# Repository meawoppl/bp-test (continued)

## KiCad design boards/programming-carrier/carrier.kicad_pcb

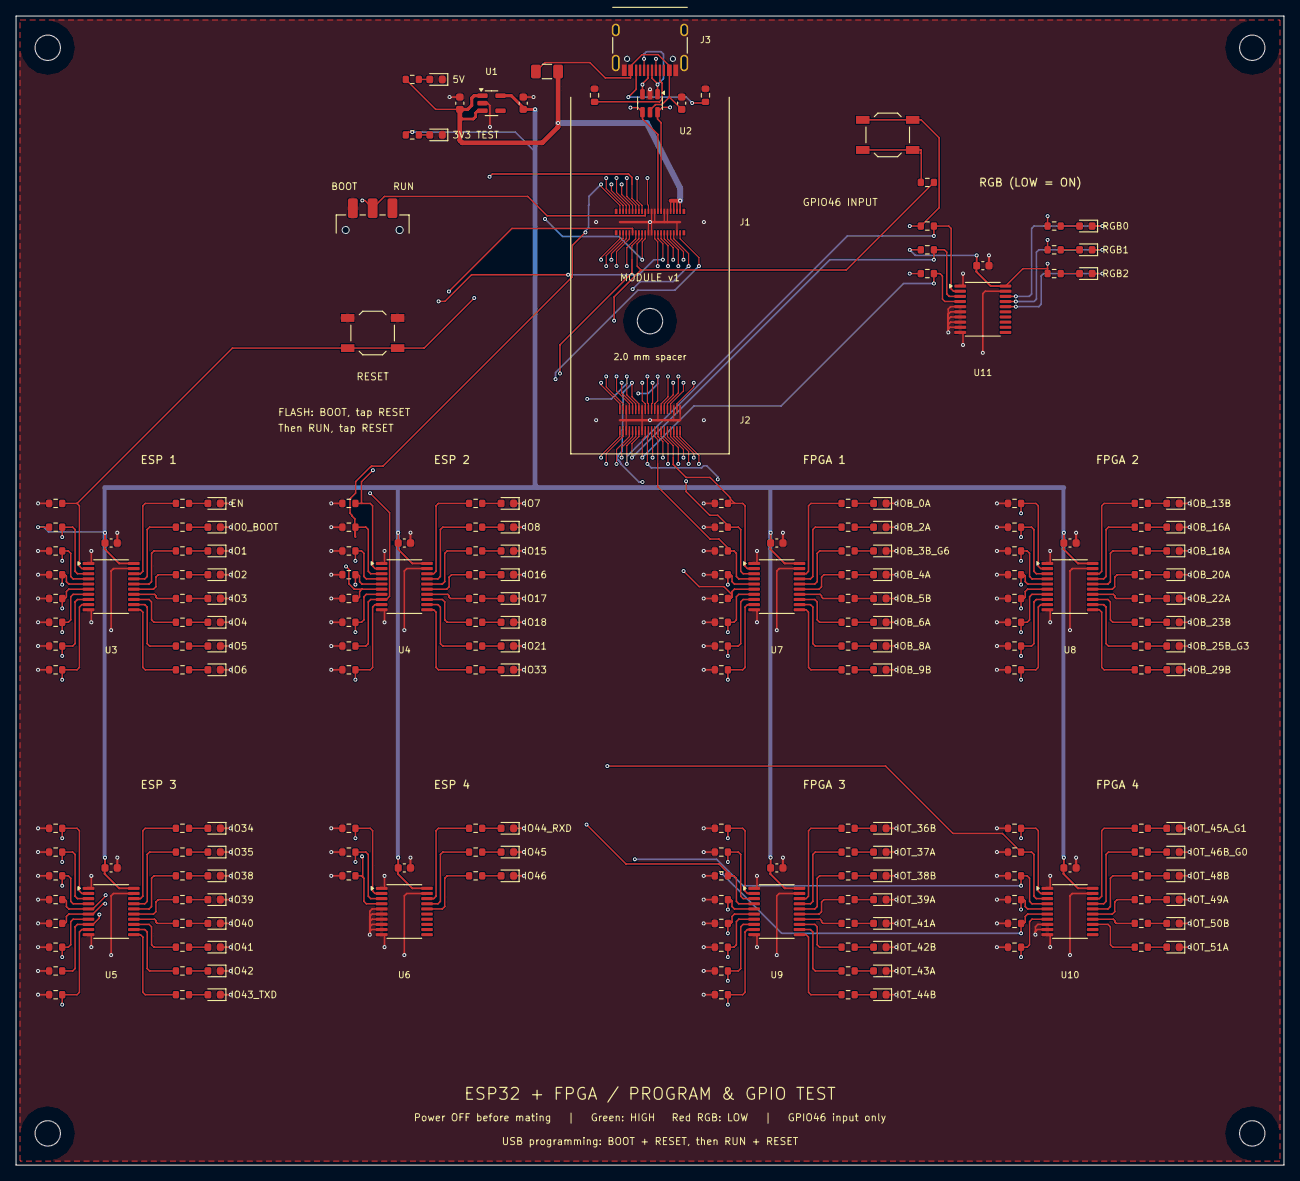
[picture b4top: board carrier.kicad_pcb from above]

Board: 4 copper layers, 160.0 x 145.0 mm, 222 parts (0 on the bottom side), 191 nets.

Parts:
C1, C2: 4.7uF; C_0603_1608Metric
C3, C10, C11, C12, C13, C14, C15, C16, C17, C18: 100nF; C_0603_1608Metric
D1, D2, D10, D11, D12, D13, D14, D15, D16, D17, D18, D19, D20, D21, D22, D23, D24, D25, D26, D27, D28, D29, D30, D31, D32, D33, D34, D35, D36, D42, D43, D44, D45, D46, D47, D48, D49, D50, D51, D52, D53, D54, D55, D56, D57, D58, D59, D60, D61, D62, D63, D64, D65, D66, D67, D68, D69, D70, D71: GREEN; LED_0603_1608Metric
D74, D75, D76: RED; LED_0603_1608Metric
F1: 500mA PTC; Fuse_1206_3216Metric
H1, H2, H3, H4, H5: M3; MountingHole_3.2mm_M3
J1: DF40C-40DP-0.4V(51); J1_Module_v1_Mate
J2: DF40C(2.0)-40DS-0.4V(51); J2_Module_v1_Mate
J3: USB-C USB2; USB_C_Receptacle_HRO_TYPE-C-31-M-12
R1, R2: 5.1kR; R_0603_1608Metric
R3: 2.2kR; R_0603_1608Metric
R4, R5, R10, R11, R12, R13, R14, R15, R16, R17, R18, R19, R20, R21, R22, R23, R24, R25, R26, R27, R28, R29, R30, R31, R32, R33, R34, R35, R36, R42, R43, R44, R45, R46, R47, R48, R49, R50, R51, R52, R53, R54, R55, R56, R57, R58, R59, R60, R61, R62, R63, R64, R65, R66, R67, R68, R69, R70, R71, R74, R75, R76: 1kR; R_0603_1608Metric
R110, R111, R112, R113, R114, R115, R116, R117, R118, R119, R120, R121, R122, R123, R124, R125, R126, R127, R128, R129, R130, R131, R132, R133, R134, R135, R136, R142, R143, R144, R145, R146, R147, R148, R149, R150, R151, R152, R153, R154, R155, R156, R157, R158, R159, R160, R161, R162, R163, R164, R165, R166, R167, R168, R169, R170, R171, R174, R175, R176: 100kR; R_0603_1608Metric
SW1: BOOT / RUN; SW_SPDT_CK_JS102011SAQN
SW2: RESET; SW_SPST_TL3342
SW3: GPIO46 INPUT; SW_SPST_TL3342
U1: AP2112K-3.3; SOT-23-5
U2: USBLC6-2SC6; SOT-23-6
U3, U4, U5, U6, U7, U8, U9, U10, U11: SN74LVC541APWR; TSSOP-20_4.4x6.5mm_P0.65mm

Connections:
+3V3_TEST: C2.1, C10.1, C11.1, C12.1, C13.1, C14.1, C15.1, C16.1, C17.1, C18.1, R4.1, R74.1, R75.1, R76.1, R111.2, R174.2, R175.2, R176.2, SW3.1, U1.5, U3.20, U4.20, U5.20, U6.20, U7.20, U8.20, U9.20, U10.20, U11.20
BUF_ESP_EN: R10.1, U3.18
BUF_ESP_GPIO0_BOOT: R11.1, U3.17
BUF_ESP_GPIO1: R12.1, U3.16
BUF_ESP_GPIO2: R13.1, U3.15
BUF_ESP_GPIO3: R14.1, U3.14
BUF_ESP_GPIO4: R15.1, U3.13
BUF_ESP_GPIO5: R16.1, U3.12
BUF_ESP_GPIO6: R17.1, U3.11
BUF_ESP_GPIO7: R18.1, U4.18
BUF_ESP_GPIO8: R19.1, U4.17
BUF_ESP_GPIO15: R20.1, U4.16
BUF_ESP_GPIO16: R21.1, U4.15
BUF_ESP_GPIO17: R22.1, U4.14
BUF_ESP_GPIO18: R23.1, U4.13
BUF_ESP_GPIO21: R24.1, U4.12
BUF_ESP_GPIO33: R25.1, U4.11
BUF_ESP_GPIO34: R26.1, U5.18
BUF_ESP_GPIO35: R27.1, U5.17
BUF_ESP_GPIO38: R28.1, U5.16
BUF_ESP_GPIO39: R29.1, U5.15
BUF_ESP_GPIO40: R30.1, U5.14
BUF_ESP_GPIO41: R31.1, U5.13
BUF_ESP_GPIO42: R32.1, U5.12
BUF_ESP_GPIO43_TXD: R33.1, U5.11
BUF_ESP_GPIO44_RXD: R34.1, U6.18
BUF_ESP_GPIO45: R35.1, U6.17
BUF_ESP_GPIO46: R36.1, U6.16
BUF_FPGA_IOB_0A: R42.1, U7.18
BUF_FPGA_IOB_2A: R43.1, U7.17
BUF_FPGA_IOB_3B_G6: R44.1, U7.16
BUF_FPGA_IOB_4A: R45.1, U7.15
BUF_FPGA_IOB_5B: R46.1, U7.14
BUF_FPGA_IOB_6A: R47.1, U7.13
BUF_FPGA_IOB_8A: R48.1, U7.12
BUF_FPGA_IOB_9B: R49.1, U7.11
BUF_FPGA_IOB_13B: R50.1, U8.18
BUF_FPGA_IOB_16A: R51.1, U8.17
BUF_FPGA_IOB_18A: R52.1, U8.16
BUF_FPGA_IOB_20A: R53.1, U8.15
BUF_FPGA_IOB_22A: R54.1, U8.14
BUF_FPGA_IOB_23B: R55.1, U8.13
BUF_FPGA_IOB_25B_G3: R56.1, U8.12
BUF_FPGA_IOB_29B: R57.1, U8.11
BUF_FPGA_IOT_36B: R58.1, U9.18
BUF_FPGA_IOT_37A: R59.1, U9.17
BUF_FPGA_IOT_38B: R60.1, U9.16
BUF_FPGA_IOT_39A: R61.1, U9.15
BUF_FPGA_IOT_41A: R62.1, U9.14
BUF_FPGA_IOT_42B: R63.1, U9.13
BUF_FPGA_IOT_43A: R64.1, U9.12
BUF_FPGA_IOT_44B: R65.1, U9.11
BUF_FPGA_IOT_45A_G1: R66.1, U10.18
BUF_FPGA_IOT_46B_G0: R67.1, U10.17
BUF_FPGA_IOT_48B: R68.1, U10.16
BUF_FPGA_IOT_49A: R69.1, U10.15
BUF_FPGA_IOT_50B: R70.1, U10.14
BUF_FPGA_IOT_51A: R71.1, U10.13
BUF_FPGA_RGB0: D74.1, U11.18
BUF_FPGA_RGB1: D75.1, U11.17
BUF_FPGA_RGB2: D76.1, U11.16
CC1: J3.A5, R1.1
CC2: J3.B5, R2.1
ESP_EN: J1.11, R110.1, SW2.2, U3.2
ESP_GPIO0_BOOT: J1.12, R111.1, SW1.2, U3.3
ESP_GPIO1: J1.13, R112.1, U3.4
ESP_GPIO2: J1.14, R113.1, U3.5
ESP_GPIO3: J1.15, R114.1, U3.6
ESP_GPIO4: J1.16, R115.1, U3.7
ESP_GPIO5: J1.17, R116.1, U3.8
ESP_GPIO6: J1.18, R117.1, U3.9
ESP_GPIO7: J1.19, R118.1, U4.2
ESP_GPIO8: J1.20, R119.1, U4.3
ESP_GPIO15: J1.35, R120.1, U4.4
ESP_GPIO16: J1.37, R121.1, U4.5
ESP_GPIO17: J1.36, R122.1, U4.6
ESP_GPIO18: J1.38, R123.1, U4.7
ESP_GPIO21: J1.40, R124.1, U4.8
ESP_GPIO33: J1.29, R125.1, U4.9
ESP_GPIO34: J1.32, R126.1, U5.2
ESP_GPIO35: J1.28, R127.1, U5.3
ESP_GPIO38: J1.39, R128.1, U5.4
ESP_GPIO39: J1.23, R129.1, U5.5
ESP_GPIO40: J1.21, R130.1, U5.6
ESP_GPIO41: J1.24, R131.1, U5.7
ESP_GPIO42: J1.25, R132.1, U5.8
ESP_GPIO43_TXD: J1.26, R133.1, U5.9
ESP_GPIO44_RXD: J1.27, R134.1, U6.2
ESP_GPIO45: J1.34, R135.1, U6.3
ESP_GPIO46: J1.33, R5.2, R136.1, U6.4
FPGA_IOB_0A: J2.35, R142.1, U7.2
FPGA_IOB_2A: J2.36, R143.1, U7.3
FPGA_IOB_3B_G6: J2.32, R144.1, U7.4
FPGA_IOB_4A: J2.37, R145.1, U7.5
FPGA_IOB_5B: J2.34, R146.1, U7.6
FPGA_IOB_6A: J2.40, R147.1, U7.7
FPGA_IOB_8A: J2.39, R148.1, U7.8
FPGA_IOB_9B: J2.38, R149.1, U7.9
FPGA_IOB_13B: J2.6, R150.1, U8.2
FPGA_IOB_16A: J2.4, R151.1, U8.3
FPGA_IOB_18A: J2.2, R152.1, U8.4
FPGA_IOB_20A: J2.7, R153.1, U8.5
FPGA_IOB_22A: J2.5, R154.1, U8.6
FPGA_IOB_23B: J2.10, R155.1, U8.7
FPGA_IOB_25B_G3: J2.12, R156.1, U8.8
FPGA_IOB_29B: J2.11, R157.1, U8.9
FPGA_IOT_36B: J2.14, R158.1, U9.2
FPGA_IOT_37A: J2.9, R159.1, U9.3
FPGA_IOT_38B: J2.15, R160.1, U9.4
FPGA_IOT_39A: J2.16, R161.1, U9.5
FPGA_IOT_41A: J2.17, R162.1, U9.6
FPGA_IOT_42B: J2.19, R163.1, U9.7
FPGA_IOT_43A: J2.20, R164.1, U9.8
FPGA_IOT_44B: J2.33, R165.1, U9.9
FPGA_IOT_45A_G1: J2.24, R166.1, U10.2
FPGA_IOT_46B_G0: J2.22, R167.1, U10.3
FPGA_IOT_48B: J2.21, R168.1, U10.4
FPGA_IOT_49A: J2.31, R169.1, U10.5
FPGA_IOT_50B: J2.25, R170.1, U10.6
FPGA_IOT_51A: J2.30, R171.1, U10.7
FPGA_RGB0: J2.26, R174.1, U11.2
FPGA_RGB1: J2.27, R175.1, U11.3
FPGA_RGB2: J2.29, R176.1, U11.4
GND: C1.2, C2.2, C3.2, C10.2, C11.2, C12.2, C13.2, C14.2, C15.2, C16.2, C17.2, C18.2, D1.1, D2.1, D10.1, D11.1, D12.1, D13.1, D14.1, D15.1, D16.1, D17.1, D18.1, D19.1, D20.1, D21.1, D22.1, D23.1, D24.1, D25.1, D26.1, D27.1, D28.1, D29.1, D30.1, D31.1, D32.1, D33.1, D34.1, D35.1, D36.1, D42.1, D43.1, D44.1, D45.1, D46.1, D47.1, D48.1, D49.1, D50.1, D51.1, D52.1, D53.1, D54.1, D55.1, D56.1, D57.1, D58.1, D59.1, D60.1, D61.1, D62.1, D63.1, D64.1, D65.1, D66.1, D67.1, D68.1, D69.1, D70.1, D71.1, J1.5, J1.6, J1.9, J1.10, J1.22, J1.30, J1.31, J2.1, J2.3, J2.8, J2.13, J2.18, J2.23, J2.28, J3.A1, J3.A12, J3.B1, J3.B12, J3.S1, R1.2, R2.2, R110.2, R112.2, R113.2, R114.2, R115.2, R116.2, R117.2, R118.2, R119.2, R120.2, R121.2, R122.2, R123.2, R124.2, R125.2, R126.2, R127.2, R128.2, R129.2, R130.2, R131.2, R132.2, R133.2, R134.2, R135.2, R136.2, R142.2, R143.2, R144.2, R145.2, R146.2, R147.2, R148.2, R149.2, R150.2, R151.2, R152.2, R153.2, R154.2, R155.2, R156.2, R157.2, R158.2, R159.2, R160.2, R161.2, R162.2, R163.2, R164.2, R165.2, R166.2, R167.2, R168.2, R169.2, R170.2, R171.2, SW1.1, SW2.1, U1.2, U2.2, U3.1, U3.10, U3.19, U4.1, U4.10, U4.19, U5.1, U5.10, U5.19, U6.1, U6.5, U6.6, U6.7, U6.8, U6.9, U6.10, U6.19, U7.1, U7.10, U7.19, U8.1, U8.10, U8.19, U9.1, U9.10, U9.19, U10.1, U10.8, U10.9, U10.10, U10.19, U11.1, U11.5, U11.6, U11.7, U11.8, U11.9, U11.10, U11.19
GPIO46_TEST: R5.1, SW3.2
LED_ESP_EN: D10.2, R10.2
LED_ESP_GPIO0_BOOT: D11.2, R11.2
LED_ESP_GPIO1: D12.2, R12.2
LED_ESP_GPIO2: D13.2, R13.2
LED_ESP_GPIO3: D14.2, R14.2
LED_ESP_GPIO4: D15.2, R15.2
LED_ESP_GPIO5: D16.2, R16.2
LED_ESP_GPIO6: D17.2, R17.2
LED_ESP_GPIO7: D18.2, R18.2
LED_ESP_GPIO8: D19.2, R19.2
LED_ESP_GPIO15: D20.2, R20.2
LED_ESP_GPIO16: D21.2, R21.2
LED_ESP_GPIO17: D22.2, R22.2
LED_ESP_GPIO18: D23.2, R23.2
LED_ESP_GPIO21: D24.2, R24.2
LED_ESP_GPIO33: D25.2, R25.2
LED_ESP_GPIO34: D26.2, R26.2
LED_ESP_GPIO35: D27.2, R27.2
LED_ESP_GPIO38: D28.2, R28.2
LED_ESP_GPIO39: D29.2, R29.2
LED_ESP_GPIO40: D30.2, R30.2
LED_ESP_GPIO41: D31.2, R31.2
LED_ESP_GPIO42: D32.2, R32.2
LED_ESP_GPIO43_TXD: D33.2, R33.2
LED_ESP_GPIO44_RXD: D34.2, R34.2
LED_ESP_GPIO45: D35.2, R35.2
LED_ESP_GPIO46: D36.2, R36.2
LED_FPGA_IOB_0A: D42.2, R42.2
LED_FPGA_IOB_2A: D43.2, R43.2
LED_FPGA_IOB_3B_G6: D44.2, R44.2
LED_FPGA_IOB_4A: D45.2, R45.2
LED_FPGA_IOB_5B: D46.2, R46.2
LED_FPGA_IOB_6A: D47.2, R47.2
LED_FPGA_IOB_8A: D48.2, R48.2
LED_FPGA_IOB_9B: D49.2, R49.2
LED_FPGA_IOB_13B: D50.2, R50.2
LED_FPGA_IOB_16A: D51.2, R51.2
LED_FPGA_IOB_18A: D52.2, R52.2
LED_FPGA_IOB_20A: D53.2, R53.2
LED_FPGA_IOB_22A: D54.2, R54.2
LED_FPGA_IOB_23B: D55.2, R55.2
LED_FPGA_IOB_25B_G3: D56.2, R56.2
LED_FPGA_IOB_29B: D57.2, R57.2
LED_FPGA_IOT_36B: D58.2, R58.2
LED_FPGA_IOT_37A: D59.2, R59.2
LED_FPGA_IOT_38B: D60.2, R60.2
LED_FPGA_IOT_39A: D61.2, R61.2
LED_FPGA_IOT_41A: D62.2, R62.2
LED_FPGA_IOT_42B: D63.2, R63.2
LED_FPGA_IOT_43A: D64.2, R64.2
LED_FPGA_IOT_44B: D65.2, R65.2
LED_FPGA_IOT_45A_G1: D66.2, R66.2
LED_FPGA_IOT_46B_G0: D67.2, R67.2
LED_FPGA_IOT_48B: D68.2, R68.2
LED_FPGA_IOT_49A: D69.2, R69.2
LED_FPGA_IOT_50B: D70.2, R70.2
LED_FPGA_IOT_51A: D71.2, R71.2
LED_FPGA_RGB0: D74.2, R74.2
LED_FPGA_RGB1: D75.2, R75.2
LED_FPGA_RGB2: D76.2, R76.2
P3_LED: D2.2, R4.2
P5_LED: D1.2, R3.2
USB_D+: J1.7, J3.A6, J3.B6, U2.1, U2.6
USB_D-: J1.8, J3.A7, J3.B7, U2.3, U2.4
VBUS: C3.1, F1.1, J3.A4, J3.A9, J3.B4, J3.B9, U2.5
VIN_5V: C1.1, F1.2, J1.1, J1.2, J1.3, J1.4, R3.1, U1.1, U1.3

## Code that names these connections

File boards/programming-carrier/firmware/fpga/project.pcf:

# GENERATED by tools/gen_pinmap.py from docs/led-map.json and the module v1 netlist.
# Do not edit by hand.

# Module-internal ESP32-S2 link (FPGA SPI configuration pins, reused at runtime)
set_io SPI_SO     14
set_io SPI_SCK    15
set_io SPI_SS_N   16
set_io SPI_SI     17

# Carrier monitor outputs: fpga_out[n] -> LED, bit order = led-map.json order
set_io fpga_out[0]  46  # D42 U7 FPGA_IOB_0A J2-35
set_io fpga_out[1]  47  # D43 U7 FPGA_IOB_2A J2-36
set_io fpga_out[2]  44  # D44 U7 FPGA_IOB_3B_G6 J2-32
set_io fpga_out[3]  48  # D45 U7 FPGA_IOB_4A J2-37
set_io fpga_out[4]  45  # D46 U7 FPGA_IOB_5B J2-34
set_io fpga_out[5]   2  # D47 U7 FPGA_IOB_6A J2-40
set_io fpga_out[6]   4  # D48 U7 FPGA_IOB_8A J2-39
set_io fpga_out[7]   3  # D49 U7 FPGA_IOB_9B J2-38
set_io fpga_out[8]   6  # D50 U8 FPGA_IOB_13B J2-6
set_io fpga_out[9]   9  # D51 U8 FPGA_IOB_16A J2-4
set_io fpga_out[10] 10  # D52 U8 FPGA_IOB_18A J2-2
set_io fpga_out[11] 11  # D53 U8 FPGA_IOB_20A J2-7
set_io fpga_out[12] 12  # D54 U8 FPGA_IOB_22A J2-5
set_io fpga_out[13] 21  # D55 U8 FPGA_IOB_23B J2-10
set_io fpga_out[14] 20  # D56 U8 FPGA_IOB_25B_G3 J2-12
set_io fpga_out[15] 19  # D57 U8 FPGA_IOB_29B J2-11
set_io fpga_out[16] 25  # D58 U9 FPGA_IOT_36B J2-14
set_io fpga_out[17] 23  # D59 U9 FPGA_IOT_37A J2-9
set_io fpga_out[18] 27  # D60 U9 FPGA_IOT_38B J2-15
set_io fpga_out[19] 26  # D61 U9 FPGA_IOT_39A J2-16
set_io fpga_out[20] 28  # D62 U9 FPGA_IOT_41A J2-17
set_io fpga_out[21] 31  # D63 U9 FPGA_IOT_42B J2-19
set_io fpga_out[22] 32  # D64 U9 FPGA_IOT_43A J2-20
set_io fpga_out[23] 34  # D65 U9 FPGA_IOT_44B J2-33
set_io fpga_out[24] 37  # D66 U10 FPGA_IOT_45A_G1 J2-24
set_io fpga_out[25] 35  # D67 U10 FPGA_IOT_46B_G0 J2-22
set_io fpga_out[26] 36  # D68 U10 FPGA_IOT_48B J2-21
set_io fpga_out[27] 43  # D69 U10 FPGA_IOT_49A J2-31
set_io fpga_out[28] 38  # D70 U10 FPGA_IOT_50B J2-25
set_io fpga_out[29] 42  # D71 U10 FPGA_IOT_51A J2-30

# RGB current sinks (SB_RGBA_DRV), shared with module D1 and carrier red monitors
set_io RGB0       39  # D74 FPGA_RGB0 J2-26
set_io RGB1       40  # D75 FPGA_RGB1 J2-27
set_io RGB2       41  # D76 FPGA_RGB2 J2-29

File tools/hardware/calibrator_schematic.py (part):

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def custom_map(ref):
 c=parts[ref]
 if ref in ['J1','J2']:
  ground=[n for n,v in c['pins'].items() if v=='GND'];supply=[n for n,v in c['pins'].items() if v in ['VIN_5V','USB_VBUS']];other=sorted([n for n in c['pins'] if n not in ground+supply],key=int);half=(len(other)+1)//2
  m={n:((-17.78 if i<half else 17.78),38.1-(i%half)*5.08,(0 if i<half else 180)) for i,n in enumerate(other)}
  m.update({n:((i-(len(ground)-1)/2)*2.54,-48.26,90) for i,n in enumerate(ground)})
  m.update({n:((i-(len(supply)-1)/2)*5.08,48.26,270) for i,n in enumerate(supply)})
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for ref,x in [('J1',73.66),('J2',205.74)]:
 place(ref,x,82.55)
 gs=[n for n,vv in parts[ref]['pins'].items() if vv=='GND'];bus(ref,gs,134.62,'GND')
 vs=[n for n,vv in parts[ref]['pins'].items() if vv in ['VIN_5V','USB_VBUS']]
 if vs:bus(ref,vs,29.21,parts[ref]['pins'][vs[0]])
 for n in parts[ref]['pins']:
  if (ref,n) not in covered:port(ref,n,7.62)
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path(P('U11',1),(438.15,33.02),(408.94,33.02));power('USB_VBUS',438.15,33.02)
place('R164',478.79,93.98,270)
path(P('U11',9),(478.79,78.74),P('R164',1));power('GND',*P('R164',2))
label('PD_ISET',466.09,78.74)
for ref,x,n,y in [('R167',478.79,'6',63.5),('R168',502.92,'7',68.58)]:
 place(ref,x,45.72,270);path(P(ref,2),(snap(x),snap(y)),P('U11',n));junction((x,y));power('+3V3_LOGIC',*P(ref,1));label(parts[ref]['pins']['2'],x,y)
note('5 V ONLY: VSET grounded / ISET 22.6k = 3 A / I2C 0x08',353.06,121.92,1.2)
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path(P('U14',3),(666.75,53.34),(666.75,44.45),(641.35,44.45));path(P('U14',4),(666.75,58.42),(666.75,53.34));junction((666.75,53.34));power('USB_VBUS',641.35,44.45)
port('U14',2,20.32)
place('R169',657.86,107.95,270);path(P('R169',1),(657.86,68.58),P('U14',2));junction((657.86,68.58));power('GND',*P('R169',2))
place('C68',673.1,102.87,270);path(P('U14',1),(692.15,87.63),(673.1,87.63),P('C68',1));label('USB_DVDT',673.1,87.63);power('GND',*P('C68',2))
place('R170',737.87,102.87,270);path(P('U14',7),(709.93,87.63),(737.87,87.63),P('R170',1));label('USB_ILIM',715.01,87.63);power('GND',*P('R170',2));bus('U14',['8','9'],81.28,'GND')
path(P('U14',5),(746.76,53.34));power('VIN_5V',746.76,53.34)
place('R176',787.4,100.33);path((737.87,87.63),(760.73,87.63),(760.73,100.33),P('R176',1));junction((737.87,87.63))
bypass('C78',805.18,121.92,'ESP_GPIO3',upper=100.33);path(P('R176',2),(805.18,100.33));label('ESP_GPIO3',805.18,100.33)
# One real power indicator, wired as LED plus its own resistor.
place('R3',774.7,58.42,270);place('D1',774.7,83.82,270)
path(P('R3',1),(774.7,45.72));power('VIN_5V',774.7,45.72)
path(P('R3',2),P('D1',2));label(parts['R3']['pins']['2'],774.7,71.12);power('GND',*P('D1',1))
note('ESP_GPIO4 enables loads; 820R sets ~2.48 A. ADC: 0.226 V/A nominal, switched loads only.',486.41,140.97,1.1)
note('Module and logic boot from raw 5 V. GPIO7/8 read PD status over I2C; firmware budgets current before enabling loads.',486.41,146.05,1.1)
# ---- GNSS receiver and active-antenna bias ------------------------------------
box('GNSS / PPS reference and active antenna bias',12.7,156.21,236.22,118.11)
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port('U6',2,10.16);port('U6',3,10.16);port('U6',5,10.16)
# One visible PPS tree: two upward, independently damped timing destinations,
# and the indicator resistor/LED directly below the common node.
path(P('U6',4),(30.48,218.44));label('GPS_PPS',91.44,218.44)
for ref,x,title in [('R6',30.48,'FPGA PPS / G0'),('R7',73.66,'ESP32 PPS / GPIO38')]:
 place(ref,x,195.58,90);path(P(ref,1),(x,218.44))
 path(P(ref,2),(x,187.96));label(parts[ref]['pins']['2'],x,187.96)
 note(title,x,176.53,1.1)
place('R179',30.48,233.68,270);place('D74',30.48,254,270)
path((30.48,218.44),P('R179',1));path(P('R179',2),P('D74',2));label('PPS_LED_A',30.48,245.11)
power('GND',*P('D74',1))
note('PPS indicator',43.18,254,1.1)
# Compact VCC_RF-powered bias tee adjacent to RF_IN.
place('R5',194.31,198.12);path(P('U6',14),P('R5',1));label('ANT_PWR',166.37,198.12)
place('L1',222.25,205.74,90);path(P('R5',2),(222.25,198.12),P('L1',2));label('ANT_BIAS',209.55,198.12)
bypass('C10',207.01,204.47,'ANT_BIAS',upper=198.12)
place('J5',238.76,218.44);path(P('U6',11),P('J5',1));label('GNSS_RF',170.18,218.44)
path(P('L1',1),(222.25,218.44));port('J5',2)
# Reset input stays below the UART/trigger labels, clear of the PPS tree.
place('R180',93.98,238.76);path(P('U6',9),P('R180',2));label('GPS_RESET_N',104.14,238.76)
port('R180',1,3.81)
def translate_section(first, previous_refs, dx, dy):
 # Move a presentation block, including its fields, power symbols and unused-pin stubs.
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box('Trigger input / 5 V TTL / threshold ~2.5 V',322.58,156.21,236.22,118.11)
place('J6',340.36,193.04);place('R8',374.65,193.04);place('U9',419.1,198.12)
# Input SMA points left graphically; lead exits and loops below the connector to R8.
path(P('J6',1),(327.66,193.04),(327.66,182.88),(359.41,182.88),(359.41,193.04),P('R8',1));label('TRIGGER_IN',346.71,182.88);port('J6',2)
path(P('R8',2),P('U9',3));label('TRIGGER_LIMIT',382.27,193.04)
bypass('C75',381,208.28,'TRIGGER_LIMIT',upper=193.04);junction((381,193.04))
place('R9',391.16,208.28,270);path(P('R9',1),(391.16,193.04));junction((391.16,193.04));power('GND',*P('R9',2))
# 2.5 V threshold divider and filter directly feed IN-.
place('R160',368.3,216.535,270);place('R161',368.3,245.11,270)
power('VIN_5V',*P('R160',1));path(P('R160',2),(368.3,231.14),P('R161',1));power('GND',*P('R161',2))
path((368.3,231.14),(401.32,231.14),(401.32,203.2),P('U9',1));label('TRIGGER_VREF',375.92,231.14)
bypass('C13',391.16,246.38,'TRIGGER_VREF',upper=231.14);junction((391.16,231.14))
bypass('C14',439.42,176.53,'VIN_5V',upper=168.91);path(P('U9',4),(419.1,168.91),(439.42,168.91));power('VIN_5V',419.1,168.91);bus('U9',['2','6'],218.44,'GND')
place('U7',480.06,193.04);path(P('U9',5),P('U7',2));label('TRIGGER_5V',441.96,193.04)
bypass('C11',501.65,175.26,'+3V3_GPS',upper=170.18);path(P('U7',5),(480.06,170.18),(501.65,170.18));power('+3V3_GPS',480.06,170.18);port('U7',3)
for ref,y in [('R80',193.04),('R81',208.28)]:
 place(ref,530.86,y);path(P('U7',4),(515.62,193.04),(515.62,snap(y)),P(ref,1));port(ref,2,3.81)
label('TRIGGER_3V3',500.38,193.04)
translate_section(section_start,section_refs,-66.04,0)
# ---- External trigger output --------------------------------------------------
box('Trigger output / 5 V TTL',500.38,156.21,139.7,118.11)
section_start=len(items);section_refs=set(placed)
# Grounded enable, input pulldown and series output damping.
place('U10',474.98,248.92);place('R162',509.27,248.92);place('J7',547.37,248.92)
path(P('U10',4),P('R162',1));label('TRIGGER_DRV',490.22,248.92);path(P('R162',2),P('J7',1));label('TRIGGER_OUT',519.43,248.92);port('J7',2)
place('R163',444.5,256.54,270);path(P('U10',2),(444.5,248.92),P('R163',1));label('FPGA_IOT_51A',429.26,248.92);path((429.26,248.92),(444.5,248.92));power('GND',*P('R163',2));bus('U10',['1','3'],267.97,'GND')
bypass('C15',501.65,231.14,'VIN_5V',upper=223.52);path(P('U10',5),(474.98,223.52),(492.76,223.52),(501.65,223.52));power('VIN_5V',492.76,223.52)
translate_section(section_start,section_refs,78.74,-40.64)
# ---- OCXO supply and clock ----------------------------------------------------
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for ref,x in [('C71',713.74),('C73',731.52),('C74',749.3)]:
 bypass(ref,x,203.2,'+3V3_OCXO',upper=189.23)
path(P('U15',5),(706.12,199.39),(706.12,189.23));bus('U15',['3','6'],227.33,'GND')
place('R178',665.48,219.71,270);path(P('R178',1),(665.48,199.39),P('U15',1));label('ESP_GPIO5',665.48,212.09,right=True);power('GND',*P('R178',2))
place('R173',805.18,222.25,270)
path(P('Y1',3),(805.18,204.47),P('R173',1));label('OCXO_CLK',800.1,204.47,right=True)
path(P('R173',2),(805.18,238.76));label(parts['R173']['pins']['2'],805.18,238.76,right=True,stub=False)
port('Y1',2)
note('SOT-223 heat spreader below OCXO; GPIO5 enables.',654.05,250.19,1.0)
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note('M3 spacer + four corner mounts.',617.22,373.38,1.0)
box('Date / UTC / GPS status OLED',706.12,281.94,119.38,97.79)
place('J8',777.24,337.82)
for ref,x,pin,net in [('R174',737.87,3,'ESP_GPIO2'),('R175',753.11,4,'ESP_GPIO1')]:
 place(ref,x,309.88,270);path(P(ref,1),(x,297.18));path(P(ref,2),(x,P('J8',pin)[1]),P('J8',pin));label(net,x-20.32,P('J8',pin)[1]);path((x-20.32,P('J8',pin)[1]),(x,P('J8',pin)[1]))
path((737.87,297.18),(753.11,297.18),(777.24,297.18));path((777.24,297.18),P('J8',2));power('+3V3_LOGIC',777.24,297.18)
for ref,x in [('C76',802.64),('C77',817.88)]:
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
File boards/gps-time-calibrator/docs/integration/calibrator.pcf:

# GPS calibrator RFC v1 reference pin constraints. Port names must match NEW HDL.
# PCF does not supply clock/CDC constraints or implement safe reset behavior.
set_io FSPI_CLK 15
set_io FSPI_MOSI 17
set_io FSPI_MISO 14
set_io FSPI_CS 16
set_io OCXO_10M 44
set_io GPS_PPS 35
set_io TRIGGER_IN 38
set_io TRIGGER_OUT 42
set_io LED_OE_N 34
set_io LED_BITS[15] 10 # J2.2, FPGA_IOB_18A
set_io LED_BITS[14] 9 # J2.4, FPGA_IOB_16A
set_io LED_BITS[13] 12 # J2.5, FPGA_IOB_22A
set_io LED_BITS[12] 6 # J2.6, FPGA_IOB_13B
set_io LED_BITS[11] 11 # J2.7, FPGA_IOB_20A
set_io LED_BITS[10] 23 # J2.9, FPGA_IOT_37A
set_io LED_BITS[9] 21 # J2.10, FPGA_IOB_23B
set_io LED_BITS[8] 19 # J2.11, FPGA_IOB_29B
set_io LED_BITS[7] 20 # J2.12, FPGA_IOB_25B_G3
set_io LED_BITS[6] 25 # J2.14, FPGA_IOT_36B
set_io LED_BITS[5] 27 # J2.15, FPGA_IOT_38B
set_io LED_BITS[4] 26 # J2.16, FPGA_IOT_39A
set_io LED_BITS[3] 28 # J2.17, FPGA_IOT_41A
set_io LED_BITS[2] 31 # J2.19, FPGA_IOT_42B
set_io LED_BITS[1] 32 # J2.20, FPGA_IOT_43A
set_io LED_BITS[0] 36 # J2.21, FPGA_IOT_48B
# Optional onboard RGB ports, only if instantiated in HDL:
# set_io RGB0 39
# set_io RGB1 40
# set_io RGB2 41

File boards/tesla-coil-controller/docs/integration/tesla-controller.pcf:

# Tesla carrier signal constraints for the UP5K-SG48 module.
# Port names must match the consuming FPGA top level.
# Generated from tesla_fpga_pinmap.py and icd-v1-pinout.csv.
# J2.2: FPGA_IOB_18A
set_io GDT2_L_HI 10
# J2.4: FPGA_IOB_16A
set_io GDT2_L_LO 9
# J2.5: FPGA_IOB_22A
set_io GDT2_R_HI 12
# J2.6: FPGA_IOB_13B
set_io GDT2_R_LO 6
# J2.7: FPGA_IOB_20A
set_io GDT1_L_HI 11
# J2.9: FPGA_IOT_37A
set_io GDT1_L_LO 23
# J2.10: FPGA_IOB_23B
set_io GDT1_R_HI 21
# J2.11: FPGA_IOB_29B
set_io GDT1_R_LO 19
# J2.22: FPGA_IOT_46B_G0
set_io CT1_ZERO 35
# J2.24: FPGA_IOT_45A_G1
set_io CT2_ZERO 37
# J2.31: FPGA_IOT_49A
set_io ADC_CONVST 43
# J2.32: FPGA_IOB_3B_G6
set_io ADC_RESET 44
# J2.33: FPGA_IOT_44B
set_io ADC_SCLK 34
# J2.34: FPGA_IOB_5B
set_io ADC_CS_N 45
# J2.35: FPGA_IOB_0A
set_io ADC_BUSY 46
# J2.36: FPGA_IOB_2A
set_io ADC_SDI 47
# J2.37: FPGA_IOB_4A
set_io ADC_DOUT_D 48
# J2.38: FPGA_IOB_9B
set_io ADC_DOUT_C 3
# J2.39: FPGA_IOB_8A
set_io ADC_DOUT_B 4
# J2.40: FPGA_IOB_6A
set_io ADC_DOUT_A 2

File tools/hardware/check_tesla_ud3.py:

#!/usr/bin/env python3
"""Independent channel contract checks and illustrative differential CT filter sweep.
Not a vendor choke macromodel: leakage is swept; no common-mode attenuation claim.
"""
import json,itertools
from pathlib import Path
import numpy as np
import matplotlib
matplotlib.use('Agg')
import matplotlib.pyplot as plt
D=Path(__file__).resolve().parents[2]/'boards/tesla-coil-controller'
p=json.loads((D/'docs/circuit.json').read_text())
from tesla_output import COMMANDS,CONTACTS
assert len(set(COMMANDS))==8
assert set(COMMANDS).issubset(p['J2']['pins'].values())
assert all(r not in p for r in ['U50','U55','C500','C501','R504'])
assert not any(n=='DRIVE_ARM' for part in p.values() for n in part['pins'].values())
for ch in range(2):
 for i in range(4):
  n=COMMANDS[ch*4+i]
  r='R'+str((505 if ch==0 else 513)+i)
  assert p[r]['pins']=={'1':n,'2':n+'_BUS'}
 for leg in range(2):
  d=p['U'+str(51+ch*2+leg)]['pins']
  assert [d['5'],d['6']]==[n+'_BUS' for n in COMMANDS[ch*4+leg*2:ch*4+leg*2+2]]
assert p['L40']['pins']=={'1':'CT1_CABLE_P','2':'CT1_RAW','4':'CT1_CABLE_N','3':'GND'}
assert p['J40']['pins']=={'1':'CT1_CABLE_P','2':'CT1_CABLE_N'}
for r in ['R400','R401','D40','C429']:assert p[r]['pins']=={'1':'CT1_RAW','2':'GND'}
assert p['C427']['pins']=={'1':'CT1_CABLE_P','2':'GND'}
assert p['C428']['pins']=={'1':'CT1_CABLE_N','2':'GND'}
def transfer(freq,leak):
 w=2*np.pi*freq;jw=1j*w;g=1/(.05+jw*leak/2)
 # Differential leakage equivalent, matched 150pF on cable conductors,
 # 1nF across 10R burden, ideal current source P->N. Both choke DCRs included.
 a=np.array([[g+jw*150e-12,0,-g],[0,g+jw*150e-12,0],[-g,0,g+.1+jw*1e-9]])
 return np.linalg.solve(a,np.array([1,-1,0]))[2]/10
f=np.geomspace(1e3,1e6,600);results=[]
plt.rcParams.update({'figure.facecolor':'#1a1b26','axes.facecolor':'#1a1b26','text.color':'#c0caf5','axes.labelcolor':'#c0caf5','xtick.color':'#c0caf5','ytick.color':'#c0caf5','axes.edgecolor':'#565f89'})
fig,axs=plt.subplots(2,1,figsize=(9,6),sharex=True)
for leak,col in zip([0,0.2e-6,2e-6],['#7aa2f7','#9ece6a','#e0af68']):
 h=np.array([transfer(x,leak) for x in f]);h30=transfer(30000,leak)
 results.append(dict(assumed_differential_leakage_uH=leak*1e6,gain_at_30k=float(abs(h30)),phase_deg_at_30k=float(np.angle(h30,deg=True)),delay_ns_at_30k=float(-np.angle(h30)/(2*np.pi*30000)*1e9)))
 axs[0].semilogx(f,20*np.log10(abs(h)),color=col,label=f'Assumed leakage {leak*1e6:g} µH')
 axs[1].semilogx(f,np.angle(h,deg=True),color=col)
for ax in axs:ax.axvline(30000,color='#bb9af7',ls='--');ax.grid(alpha=.18)
axs[0].set_ylabel('Gain relative to 10 Ω burden (dB)');axs[1].set_ylabel('Added phase (degrees)');axs[1].set_xlabel('Frequency (Hz)');axs[0].legend(facecolor='#1a1b26',labelcolor='#c0caf5')
fig.suptitle('CT input filter: differential small-signal model\nIdeal CT, linear parts; choke leakage assumed, not measured')
fig.tight_layout();out=D/'docs/cst';out.mkdir(exist_ok=True)
fig.savefig(out/'cable-filter-response.png',dpi=160)
(out/'cable-filter-results.json').write_text(json.dumps({'model':'Ideal current source, 50mΩ/winding, 150pF cable shunts, 1nF burden shunt; no TVS/cable/CT parasitics or core saturation','results':results},indent=2)+'\n')
print('Independent command paths and filter topology verified.');print(json.dumps(results,indent=2))

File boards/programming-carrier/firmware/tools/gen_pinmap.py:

#!/usr/bin/env python3
"""Generate the fixture PCF and ESP channel table from the carrier LED map.

Inputs:
  docs/led-map.json                                  carrier monitor channels
  ../esp32-fpga-module/fab/checks/module-netlist.xml module v1 connector/package pins

Outputs:
  firmware/fpga/project.pcf
  firmware/firmware/main/carrier_map.h

Run from anywhere: python3 boards/programming-carrier/firmware/tools/gen_pinmap.py
"""
import json
import re
import xml.etree.ElementTree as ET
from pathlib import Path

HERE = Path(__file__).resolve().parent
PROJECT = HERE.parent
CARRIER = PROJECT.parent
LED_MAP = CARRIER / "docs/led-map.json"
NETLIST = CARRIER.parent / "esp32-fpga-module/fab/checks/module-netlist.xml"

# FPGA pins used by the module-internal ESP32 link (LINK_* nets).
FPGA_SPI = {"SPI_SO": "LINK_MISO", "SPI_SCK": "LINK_SCK", "SPI_SS_N": "LINK_CS_N", "SPI_SI": "LINK_MOSI"}

# README "Pin classes": what the firmware may do with each ESP signal.
ESP_CLASS = {
    "ESP_EN": "CH_OBSERVE",          # chip enable; SW2 reset tests it
    "ESP_GPIO0_BOOT": "CH_OBSERVE",  # boot strap; SW1 controls it
    "ESP_GPIO45": "CH_OPT_IN",       # flash-voltage strap; separate opt-in test
    "ESP_GPIO46": "CH_INPUT",        # input only; SW3 button
}


def load_nets():
    root = ET.parse(NETLIST).getroot()
    nets = {}
    for net in root.iter("net"):
        name = net.get("name").lstrip("/")
        nets[name] = {n.get("ref"): n.get("pin") for n in net.iter("node")}
    return nets


def main():
    leds = json.loads(LED_MAP.read_text())
    nets = load_nets()

    channels = []
    fpga_bit = 0
    for e in leds:
        sig = e["signal"]
        nodes = nets[sig]
        conn = "J1" if "J1" in nodes else "J2"
        ch = {
            "signal": sig,
            "led": e["led"],
            "buffer": e["buffer"],
            "bank": e["bank"],
            "active_low": e["active_low"],
            "conn": conn,
            "conn_pin": int(nodes[conn]),
        }
        if e["bank"] == "ESP":
            ch["pkg_pin"] = int(nodes["U1"])
            m = re.match(r"ESP_GPIO(\d+)", sig)
            ch["gpio"] = int(m.group(1)) if m else -1
            ch["cls"] = ESP_CLASS.get(sig, "CH_OUTPUT")
            ch["index"] = ch["gpio"]
        elif e["bank"] == "FPGA":
            ch["pkg_pin"] = int(nodes["U2"])
            ch["cls"] = "CH_OUTPUT"
            ch["index"] = fpga_bit
            fpga_bit += 1
        else:
            ch["pkg_pin"] = int(nodes["U2"])
            ch["cls"] = "CH_RGB"
            ch["index"] = int(sig[-1])
        channels.append(ch)

    assert fpga_bit == 30, fpga_bit

    # ---- PCF ----
    pcf = [
        "# GENERATED by tools/gen_pinmap.py from docs/led-map.json and the module v1 netlist.",
        "# Do not edit by hand.",
        "",
        "# Module-internal ESP32-S2 link (FPGA SPI configuration pins, reused at runtime)",
    ]
    for port, net in FPGA_SPI.items():
        pcf.append(f"set_io {port:<10} {nets[net]['U2']}")
    pcf += ["", "# Carrier monitor outputs: fpga_out[n] -> LED, bit order = led-map.json order"]
    for ch in channels:
        if ch["bank"] == "FPGA":
            port = f"fpga_out[{ch['index']}]"
            pcf.append(f"set_io {port:<12} {ch['pkg_pin']:>2}  # {ch['led']} {ch['buffer']} {ch['signal']} {ch['conn']}-{ch['conn_pin']}")
    pcf += ["", "# RGB current sinks (SB_RGBA_DRV), shared with module D1 and carrier red monitors"]
    for ch in channels:
        if ch["bank"] == "RGB":
            pcf.append(f"set_io RGB{ch['index']:<7} {ch['pkg_pin']}  # {ch['led']} {ch['signal']} {ch['conn']}-{ch['conn_pin']}")
    (PROJECT / "fpga/project.pcf").write_text("\n".join(pcf) + "\n")

    # ---- C header ----
    banks = []
    for ch in channels:
        if ch["buffer"] not in banks:
            banks.append(ch["buffer"])
    h = [
        "// GENERATED by tools/gen_pinmap.py from docs/led-map.json and the module v1 netlist.",
        "// Do not edit by hand.",
        "#pragma once",
        "",
        "#include \"carrier_types.h\"",
        "",
        f"#define CARRIER_CHANNEL_COUNT {len(channels)}",
        f"#define CARRIER_BANK_COUNT {len(banks)}",
        "",
        "// Physical order: grouped by buffer, input-pin order within each buffer.",
        "static const carrier_channel_t CARRIER_CHANNELS[CARRIER_CHANNEL_COUNT] = {",
    ]
    for ch in channels:
        kind = {"ESP": "KIND_ESP", "FPGA": "KIND_FPGA", "RGB": "KIND_RGB"}[ch["bank"]]
        h.append(
            f'    {{ "{ch["signal"]}", "{ch["led"]}", "{ch["buffer"]}", {kind}, {ch["cls"]}, '
            f'{ch["index"]}, "{ch["conn"]}", {ch["conn_pin"]}, {ch["pkg_pin"]}, {str(ch["active_low"]).lower()} }},'
        )
    h += ["};", "", "static const char *const CARRIER_BANKS[CARRIER_BANK_COUNT] = {"]
    h += [f'    "{b}",' for b in banks]
    h += ["};", ""]
    (PROJECT / "firmware/main/carrier_map.h").write_text("\n".join(h))


if __name__ == "__main__":
    main()
